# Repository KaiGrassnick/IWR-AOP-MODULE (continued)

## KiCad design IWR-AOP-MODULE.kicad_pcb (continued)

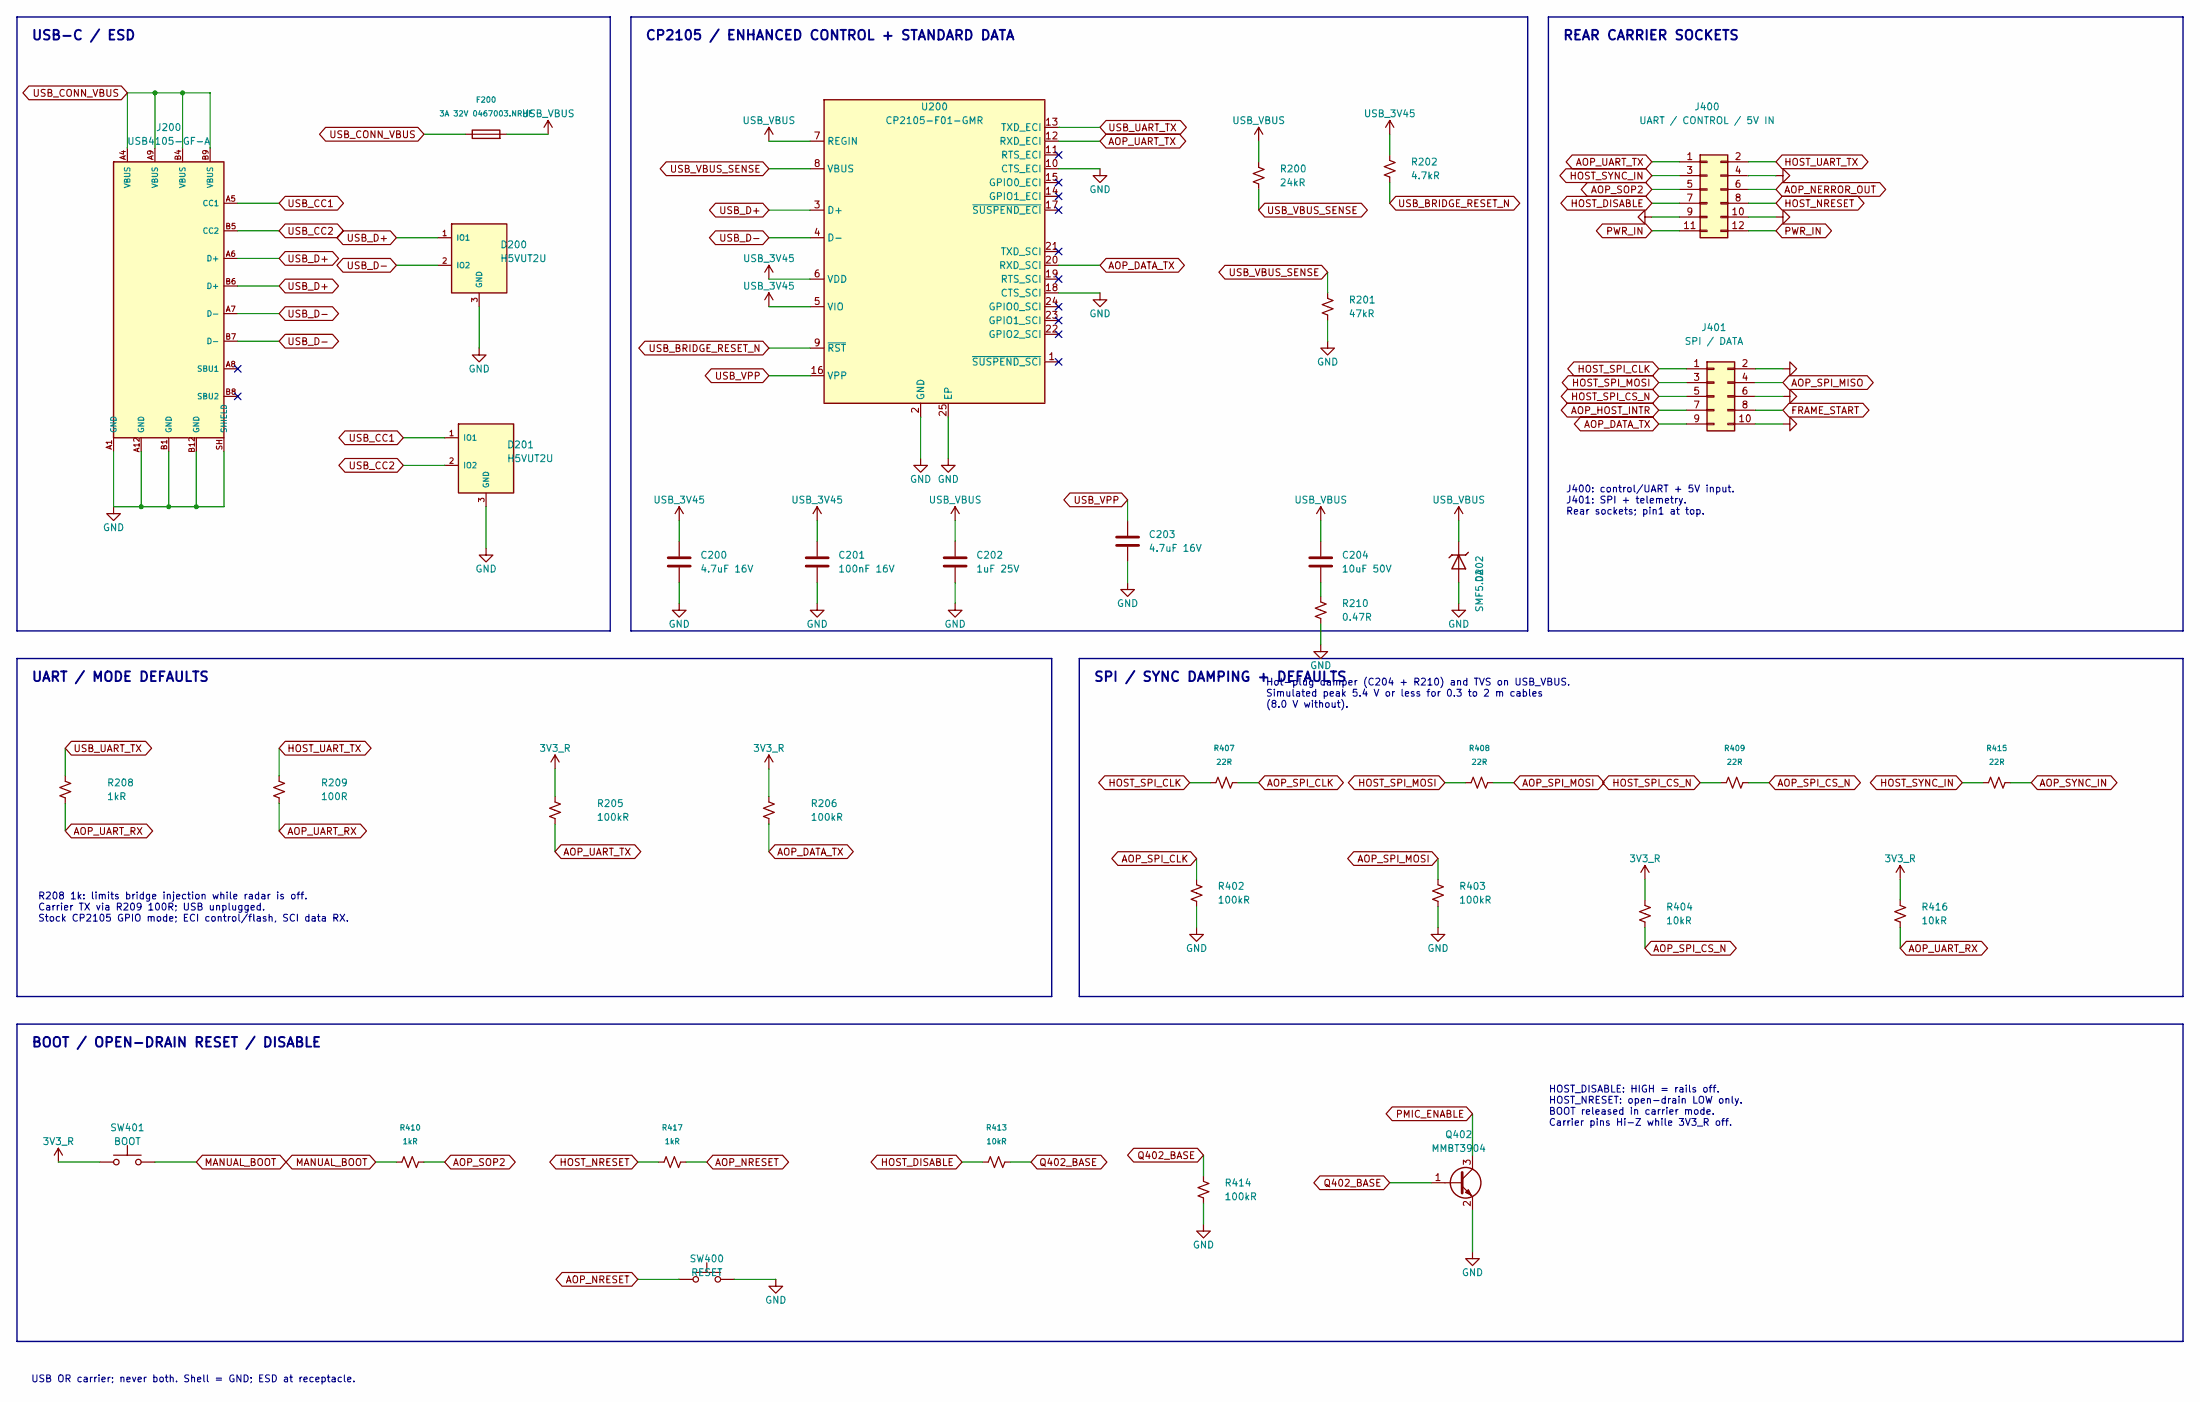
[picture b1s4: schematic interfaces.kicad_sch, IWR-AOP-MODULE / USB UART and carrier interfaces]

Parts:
C200, C203: 4.7uF 16V; C_0805_2012Metric; MPN CL21A475KAQNNNE; LCSC C1779
C201: 100nF 16V; C_0402_1005Metric; MPN CL05B104KO5NNNC; LCSC C1525
C202: 1uF 25V; C_0805_2012Metric; MPN CL21B105KBFNNNE; LCSC C28323
C204: 10uF 50V; C_1206_3216Metric; MPN CL31A106KBHNNNE; LCSC C13585
D200, D201: H5VUT2U; SOT-23; MPN H5VUT2U; LCSC C20615824
D202: SMF5.0A; D_SOD-123F; MPN SMF5.0A; LCSC C193402
F200: 3A 32V 0467003.NRHF; Fuse_0603_1608Metric; MPN 0467003.NRHF; LCSC C99558
J200: USB4105-GF-A; USB_C_Receptacle_GCT_USB4105-xx-A_16P_TopMnt_Horizontal; MPN USB4105-GF-A; LCSC C3020560
J400: UART / CONTROL / 5V IN; HCTL_PM254-2-06-S-8.5; MPN PM254-2-06-S-8.5; LCSC C3975151
J401: SPI / DATA; HCTL_PM254-2-05-S-8.5; MPN PM254-2-05-S-8.5; LCSC C3975150
Q402: MMBT3904; SOT-23; MPN MMBT3904; LCSC C20526
R200: 24kR; R_0402_1005Metric; MPN 0402WGF2402TCE; LCSC C25769
R201: 47kR; R_0402_1005Metric; MPN 0402WGF4702TCE; LCSC C25792
R202: 4.7kR; R_0402_1005Metric; MPN 0402WGF4701TCE; LCSC C25900
R205, R206, R402, R403, R414: 100kR; R_0402_1005Metric; MPN 0402WGF1003TCE; LCSC C25741
R208, R410, R417: 1kR; R_0402_1005Metric; MPN 0402WGF1001TCE; LCSC C11702
R209: 100R; R_0402_1005Metric; MPN 0402WGF1000TCE; LCSC C25076
R210: 0.47R; R_0603_1608Metric; MPN 0603WAF470LT5E; LCSC C23411
R404, R413, R416: 10kR; R_0402_1005Metric; MPN 0402WGF1002TCE; LCSC C25744
R407, R408, R409, R415: 22R; R_0402_1005Metric; MPN 0402WGF220JTCE; LCSC C25092
SW400: RESET; XKB_TS-1187A-B-A-B_5.1x5.1mm; MPN TS-1187A-B-A-B; LCSC C318884
SW401: BOOT; XKB_TS-1187A-B-A-B_5.1x5.1mm; MPN TS-1187A-B-A-B; LCSC C318884
U200: CP2105-F01-GMR; QFN-24-1EP_4x4mm_P0.5mm_EP2.7x2.6mm; MPN CP2105-F01-GMR; LCSC C109102

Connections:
3V3_R: R205.1, R206.1, R404.1, R416.1, SW401.1; also elsewhere on the board
AOP_DATA_TX: J401.9, R206.2, U200.20 (RXD_SCI); also elsewhere on the board
AOP_HOST_INTR: J401.7; also elsewhere on the board
AOP_NERROR_OUT: J400.6; also elsewhere on the board
AOP_NRESET: R417.2, SW400.1; also elsewhere on the board
AOP_SOP2: J400.5, R410.2; also elsewhere on the board
AOP_SPI_CLK: R402.1, R407.2; also elsewhere on the board
AOP_SPI_CS_N: R404.2, R409.2; also elsewhere on the board
AOP_SPI_MISO: J401.4; also elsewhere on the board
AOP_SPI_MOSI: R403.1, R408.2; also elsewhere on the board
AOP_SYNC_IN: R415.2; also elsewhere on the board
AOP_UART_RX: R208.2, R209.2, R416.2; also elsewhere on the board
AOP_UART_TX: J400.1, R205.2, U200.12 (RXD_ECI); also elsewhere on the board
FRAME_START: J401.8; also elsewhere on the board
GND: C200.2, C201.2, C202.2, C203.2, D200.3 (GND), D201.3 (GND), D202.2 (A), J200.A1 (GND), J200.A12 (GND), J200.B1 (GND), J200.B12 (GND), J200.SH (SHIELD), J400.4, J400.9, J400.10, J401.2, J401.6, J401.10, Q402.2 (E), R201.2, R210.2, R402.2, R403.2, R414.2, SW400.2, U200.2 (GND), U200.10 (CTS_ECI), U200.18 (CTS_SCI), U200.25 (EP); also elsewhere on the board
HOST_DISABLE: J400.7, R413.1
HOST_NRESET: J400.8, R417.1
HOST_SPI_CLK: J401.1, R407.1
HOST_SPI_CS_N: J401.5, R409.1
HOST_SPI_MOSI: J401.3, R408.1
HOST_SYNC_IN: J400.3, R415.1
HOST_UART_TX: J400.2, R209.1
MANUAL_BOOT: R410.1, SW401.2
unnamed: C204.2, R210.1
PMIC_ENABLE: Q402.3 (C); also elsewhere on the board
PWR_IN: J400.11, J400.12; also elsewhere on the board
Q402_BASE: Q402.1 (B), R413.2, R414.1
USB_3V45: C200.1, C201.1, R202.1, U200.5 (VIO), U200.6 (VDD)
USB_BRIDGE_RESET_N: R202.2, U200.9 (~RST)
USB_CC1: D201.1 (IO1), J200.A5 (CC1); also elsewhere on the board
USB_CC2: D201.2 (IO2), J200.B5 (CC2); also elsewhere on the board
USB_CONN_VBUS: F200.1, J200.A4 (VBUS), J200.A9 (VBUS), J200.B4 (VBUS), J200.B9 (VBUS)
USB_D+: D200.1 (IO1), J200.A6 (D+), J200.B6 (D+), U200.3 (D+)
USB_D-: D200.2 (IO2), J200.A7 (D-), J200.B7 (D-), U200.4 (D-)
USB_UART_TX: R208.1, U200.13 (TXD_ECI)
USB_VBUS: C202.1, C204.1, D202.1 (K), F200.2, R200.1, U200.7 (REGIN); also elsewhere on the board
USB_VBUS_SENSE: R200.2, R201.1, U200.8 (VBUS)
USB_VPP: C203.1, U200.16 (VPP)

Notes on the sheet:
USB-C / ESD
CP2105 / ENHANCED CONTROL + STANDARD DATA
REAR CARRIER SOCKETS
J400: control/UART + 5V input. J401: SPI + telemetry. Rear sockets; pin1 at top.
UART / MODE DEFAULTS
R208 1k: limits bridge injection while radar is off. Carrier TX via R209 100R; USB unplugged. Stock CP2105 GPIO mode; ECI control/flash, SCI data RX.
SPI / SYNC DAMPING + DEFAULTS
BOOT / OPEN-DRAIN RESET / DISABLE
HOST_DISABLE: HIGH = rails off. HOST_NRESET: open-drain LOW only. BOOT released in carrier mode. Carrier pins Hi-Z while 3V3_R off.
USB OR carrier; never both. Shell = GND; ESD at receptacle.
Hot-plug damper (C204 + R210) and TVS on USB_VBUS. Simulated peak 5.4 V or less for 0.3 to 2 m cables (8.0 V without).

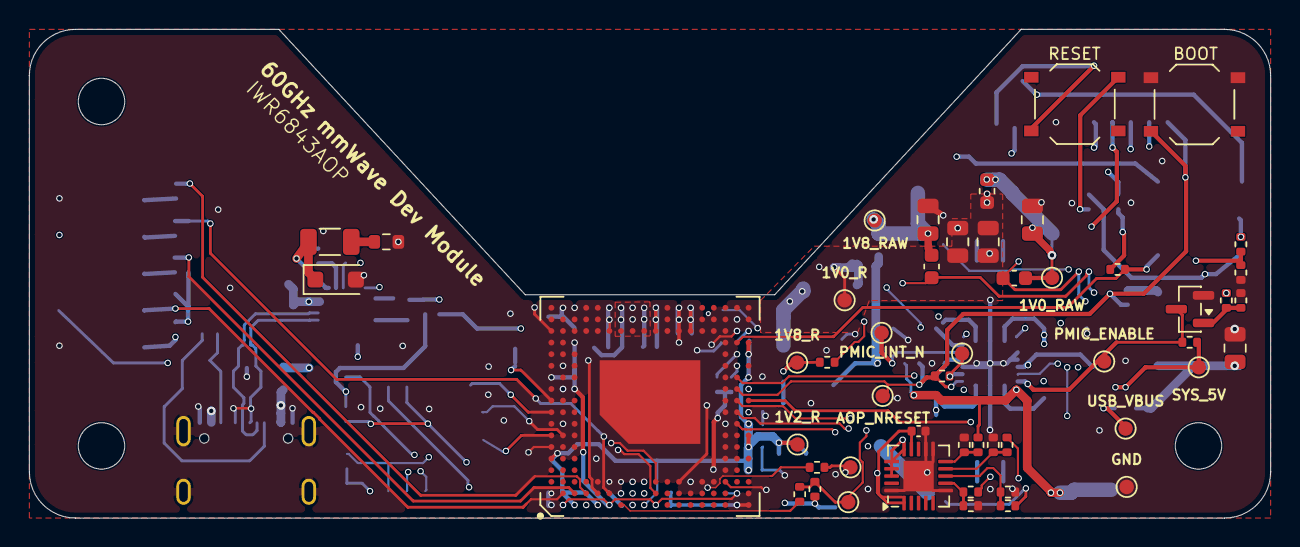
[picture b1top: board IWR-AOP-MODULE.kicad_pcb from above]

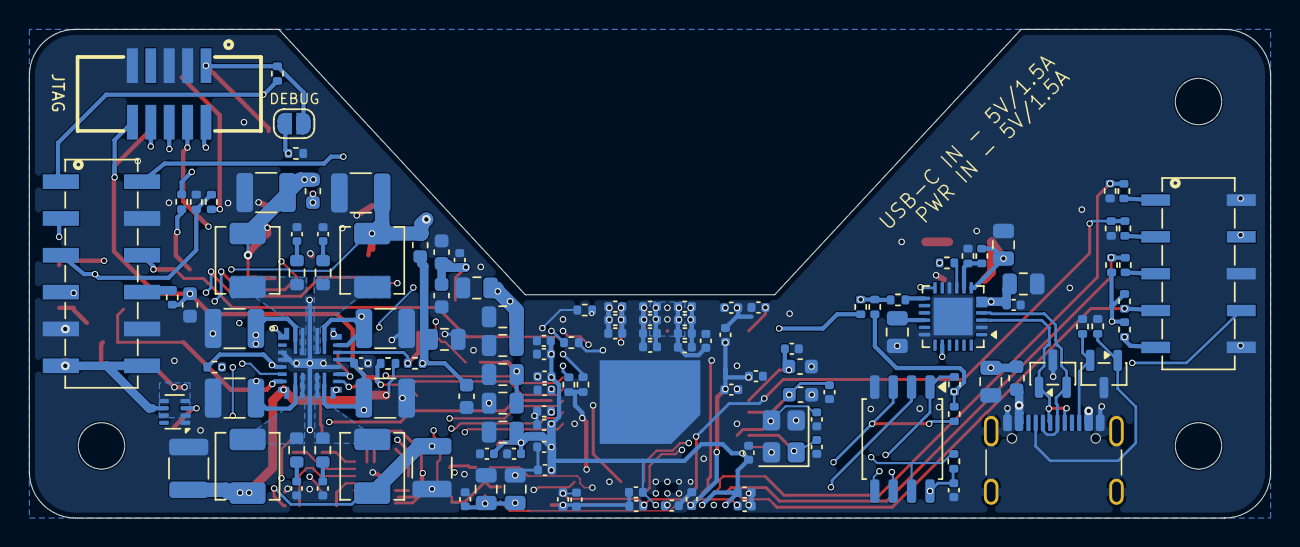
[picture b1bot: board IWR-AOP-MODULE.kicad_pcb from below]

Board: 6 copper layers, 85.6 x 33.7 mm, 186 parts (132 on the bottom side), 83 nets.

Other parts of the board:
H1, H3, H4: MountingHole_3.2mm_M3
HS300: Heat sink 14x14x6 (HSB03-141406 / ICK BGA 14x14x6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
TH300: AOP_ALP180_DieThermalPad

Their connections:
GND: TH300.1; also elsewhere on the board

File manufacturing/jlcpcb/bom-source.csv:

"Comment","Designator","Footprint","LCSC","Qty","MPN","Manufacturer","Tolerance","Rating"
"0R","R314,R605,R606","Resistor_SMD:R_0402_1005Metric","C17168","3","0402WGF0000TCE","UNI-ROYAL(Uniroyal Elec)","",""
"18pF","C346,C347","Capacitor_SMD:C_0402_1005Metric","C1549","2","0402CG180J500NT","FH (Guangdong Fenghua Advanced Tech)","",""
"390pF","C614,C615,C616,C617","Capacitor_SMD:C_0402_1005Metric","C76967","4","GRM1555C1H391JA01D","Murata Electronics","5%","C0G 50V"
"47nF","C345","Capacitor_SMD:C_0402_1005Metric","C77017","1","GRM155R71E473KA88D","Murata","",""
"100nF","C301,C302,C303,C304,C305,C306,C307,C308,C309,C310,C311,C314,C315,C316,C317,C318,C319,C322,C323,C324,C325,C326,C327,C328,C329,C330,C331,C332,C333,C335,C336,C338,C340,C342,C343,C344,C348,C604,C606,C622,C623,C706","Capacitor_SMD:C_0402_1005Metric","C1525","42","CL05B104KO5NNNC","Samsung Electro-Mechanics","",""
"0.47uH","L600,L601,L602,L603","Inductor_SMD:L_Sunlord_MWSA0402S","C6331050","4","MWSA0402S-R47MT","Sunlord","",""
"1uF","C313,C321,C337,C339","Capacitor_SMD:C_0603_1608Metric","C15849","4","CL10A105KB8NNNC","Samsung Electro-Mechanics","",""
"1uF","C631,C632","Capacitor_SMD:C_0603_1608Metric","C15849","2","CL10A105KB8NNNC","Samsung Electro-Mechanics","","X5R 50V"
"4.7uF","C341","Capacitor_SMD:C_0603_1608Metric","C19666","1","CL10A475KO8NNNC","Samsung Electro-Mechanics","",""
"10uF","C300,C312,C320,C334","Capacitor_SMD:C_0805_2012Metric","C15850","4","CL21A106KAYNNNE","Samsung Electro-Mechanics","",""
"10uF","C620,C621,C629","Capacitor_SMD:C_0805_2012Metric","C86038","3","GRM21BR71A106KE51L","Murata Electronics","10%","X7R 10V"
"22uF","C600,C601,C602,C603,C610,C611,C612,C613","Capacitor_SMD:C_1210_3225Metric","C21397","8","GRM32ER71E226KE15L","Murata Electronics","10%","X7R 25V"
"22uF","C624,C625,C626,C628,C630,C633","Capacitor_SMD:C_0805_2012Metric","C45783","6","CL21A226MAQNNNE","Samsung Electro-Mechanics","20%","X5R 25V"
"0.47R","R210","Resistor_SMD:R_0603_1608Metric","C23411","1","0603WAF470LT5E","UNI-ROYAL(Uniroyal Elec)","",""
"1kR","R208,R410,R417","Resistor_SMD:R_0402_1005Metric","C11702","3","0402WGF1001TCE","UNI-ROYAL(Uniroyal Elec)","",""
"3.9R","R610,R611,R612,R613","Resistor_SMD:R_0603_1608Metric","C482845","4","RC0603FR-073R9L","YAGEO","1%","100mW"
"4.7kR","R202","Resistor_SMD:R_0402_1005Metric","C25900","1","0402WGF4701TCE","UNI-ROYAL(Uniroyal Elec)","",""
"10kR","R133,R300,R304,R305,R306,R307,R308,R309,R310,R311,R312,R313,R404,R413,R416,R600,R601,R602,R603","Resistor_SMD:R_0402_1005Metric","C25744","19","0402WGF1002TCE","UNI-ROYAL(Uniroyal Elec)","",""
"12kR","R627","Resistor_SMD:R_0402_1005Metric","C25752","1","0402WGF1202TCE","UNI-ROYAL(Uniroyal Elec)","",""
"15kR","R621,R623,R625,R626","Resistor_SMD:R_0402_1005Metric","C25756","4","0402WGF1502TCE","UNI-ROYAL(Uniroyal Elec)","",""
"22R","R407,R408,R409,R415,R628,R629","Resistor_SMD:R_0402_1005Metric","C25092","6","0402WGF220JTCE","UNI-ROYAL(Uniroyal Elec)","",""
"24kR","R200","Resistor_SMD:R_0402_1005Metric","C25769","1","0402WGF2402TCE","UNI-ROYAL(Uniroyal Elec)","",""
"27kR","R624","Resistor_SMD:R_0402_1005Metric","C25771","1","0402WGF2702TCE","UNI-ROYAL(Uniroyal Elec)","",""
"47kR","R201,R622","Resistor_SMD:R_0402_1005Metric","C25792","2","0402WGF4702TCE","UNI-ROYAL(Uniroyal Elec)","",""
"100R","R209","Resistor_SMD:R_0402_1005Metric","C25076","1","0402WGF1000TCE","UNI-ROYAL(Uniroyal Elec)","",""
"100kR","R205,R206,R402,R403,R414,R620","Resistor_SMD:R_0402_1005Metric","C25741","6","0402WGF1003TCE","UNI-ROYAL(Uniroyal Elec)","",""
"40MHz","Y300","Crystal:Crystal_SMD_3225-4Pin_3.2x2.5mm","C18214314","1","XL2EL89COI-111YLC-40M","YXC Crystal Oscillators","",""
"100nF 16V","C201","Capacitor_SMD:C_0402_1005Metric","C1525","1","CL05B104KO5NNNC","Samsung Electro-Mechanics","",""
"10uF 10V","C140","Capacitor_SMD:C_0805_2012Metric","C86038","1","GRM21BR71A106KE51L","Murata Electronics","",""
"10uF 50V","C204","Capacitor_SMD:C_1206_3216Metric","C13585","1","CL31A106KBHNNNE","Samsung Electro-Mechanics","",""
"1uF 25V","C100,C202","Capacitor_SMD:C_0805_2012Metric","C28323","2","CL21B105KBFNNNE","Samsung Electro-Mechanics","",""
"26R@100MHz / 6A","FB600,FB601,FB602","Inductor_SMD:L_0603_1608Metric","C88981","3","BLM18KG260TN1D","Murata","",""
"3A 32V 0467003.NRHF","F200","Fuse:Fuse_0603_1608Metric","C99558","1","0467003.NRHF","Littelfuse","",""
"4.7uF 16V","C200,C203","Capacitor_SMD:C_0805_2012Metric","C1779","2","CL21A475KAQNNNE","Samsung Electro-Mechanics","",""
"5.1kR 1%","R100,R101","Resistor_SMD:R_0402_1005Metric","C25905","2","0402WGF5101TCE","UNI-ROYAL(Uniroyal Elec)","",""
"BOOT","SW401","IWR-AOP-MODULE:XKB_TS-1187A-B-A-B_5.1x5.1mm","C318884","1","TS-1187A-B-A-B","XKB Connection","",""
"CP2105-F01-GMR","U200","Package_DFN_QFN:QFN-24-1EP_4x4mm_P0.5mm_EP2.7x2.6mm","C109102","1","CP2105-F01-GMR","Silicon Laboratories","",""
"H5VUT2U","D200,D201","Package_TO_SOT_SMD:SOT-23","C20615824","2","H5VUT2U","hongjiacheng","",""
"IWR6843ARQGALPR","U300","IWR-AOP-MODULE:BGA180C80P18X18_1500X1500X97N","C2871887","1","IWR6843ARQGALPR","Texas Instruments","",""
"LM66200DRLR","U117","Package_TO_SOT_SMD:SOT-583-8","C3235556","1","LM66200DRLR","Texas Instruments","",""
"LP87524JRNFRQ1","U600","IWR-AOP-MODULE:Texas_RNF0026C_LP87524J","C701982","1","LP87524JRNFRQ1","Texas Instruments","",""
"MMBT3904","Q402","Package_TO_SOT_SMD:SOT-23","C20526","1","MMBT3904","Jiangsu Changjing Electronics Technology Co., Ltd.","",""
"MX25L3233FM2I-08G","U301","Package_SO:SOIC-8_5.3x5.3mm_P1.27mm","C190802","1","MX25L3233FM2I-08G","Macronix","",""
"RADAR JTAG","J301","IWR-AOP-MODULE:XKB_X1270WVS-2x05B-9TV01_2x05_P1.27mm_Vertical","C2962219","1","X1270WVS-2x05B-9TV01","XKB Connection","",""
"RESET","SW400","IWR-AOP-MODULE:XKB_TS-1187A-B-A-B_5.1x5.1mm","C318884","1","TS-1187A-B-A-B","XKB Connection","",""
"SMF5.0A","D202","Diode_SMD:D_SOD-123F","C193402","1","SMF5.0A","ElecSuper","",""
"SPI / DATA","J401","IWR-AOP-MODULE:HCTL_PM254-2-05-S-8.5","C3975150","1","PM254-2-05-S-8.5","HCTL","",""
"TPS386000RGPR","U601","Package_DFN_QFN:TQFN-20-1EP_4x4mm_P0.5mm_EP2.1x2.1mm","C702221","1","TPS386000RGPR","Texas Instruments","",""
"UART / CONTROL / 5V IN","J400","IWR-AOP-MODULE:HCTL_PM254-2-06-S-8.5","C3975151","1","PM254-2-06-S-8.5","HCTL","",""
"USB4105-GF-A","J200","Connector_USB:USB_C_Receptacle_GCT_USB4105-xx-A_16P_TopMnt_Horizontal","C3020560","1","USB4105-GF-A","Global Connector Technology","",""

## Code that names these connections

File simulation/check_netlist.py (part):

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      "14": "1V2_R", "15": "AOP_NRESET", "16": "PMIC_PGOOD", "17": "GND", "18": "SYS_5V",
      "19": "PMIC_INT_N", "20": "SYS_5V", "21": "/Radar PMIC/FB_B3", "22": "SYS_5V", "23": "PMIC_SW3",
      "24": "GND", "25": "PMIC_SW2", "26": "SYS_5V", "27": "GND"}
names = {"1": "FB_B2", "3": "CLKIN", "7": "EN1", "8": "FB_B0", "14": "FB_B1", "15": "EN2/GPIO2",
         "16": "PGOOD", "18": "VANA", "20": "NRST", "21": "FB_B3"}
for pad, want in lp.items():
    chk(f"U600 LP87524J pin {pad} {names.get(pad, '')}", pin("U600", pad) == want, f"{pin('U600', pad)} (want {want})")
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        ok and vmax < lo_reg, f"band starts at {lo_reg:.3f} V")
chk("R604 not fitted: PGOOD is not a reset source", "dnp" in P["R604"].get("attr", []))
# radar I2C master to the PMIC (SWRS237C pin-mux: G3 I2C_SCL mode 2, G1 I2C_SDA mode 2)
chk("U300 G3 (I2C_SCL) -> R605 -> PMIC_SCL", pin("U300", "G3") == "AOP_I2C_SCL" and set(P["R605"]["pads"].values()) == {"AOP_I2C_SCL", "PMIC_SCL"})
chk("U300 G1 (I2C_SDA) -> R606 -> PMIC_SDA", pin("U300", "G1") == "AOP_I2C_SDA" and set(P["R606"]["pads"].values()) == {"AOP_I2C_SDA", "PMIC_SDA"})
# USB hot-plug damper and TVS
chk("C204 + R210 series damper across USB_VBUS", P["C204"]["pads"]["1"] == "USB_VBUS" and P["C204"]["pads"]["2"] == P["R210"]["pads"]["1"]
    and P["R210"]["pads"]["2"] == "GND", f"{P['C204']['value']} + {P['R210']['value']}")
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
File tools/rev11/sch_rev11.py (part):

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        def fn(l):
            return l.replace(f'IWR-AOP-MODULE:PWR_{a}"', f'IWR-AOP-MODULE:PWR_{b}"').replace(f'"Value" "{a}"', f'"Value" "{b}"')
        return fn
    # FB_B2 / FB_B3: the power symbol on each feedback pin becomes a net label; the sense network
    # (R628/C631, R629/C632) is drawn in the supervisor block below.
    for pwr, fb in (("#PWR8028", "FB_B2"), ("#PWR8038", "FB_B3")):
        i = s.idx(pwr)
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    s.edit("#PWR8046", swap("1V8_R", "3V3_R"))
    # PGOOD is no longer a reset source by default
    s.edit("R604", lambda l: prop(l.replace("(dnp no)", "(dnp yes)"), "Description",
                                  "DNP option: fitted, PGOOD also asserts reset. Not fitted, reset is U601 + GPIO2."))
    # Ferrites: BLM18KG260TN1D (26 ohm, 6 A, 7 mohm max) in place of the 120 ohm part of the TI EVM. About a
    # quarter of the inductance: the filter still meets the 4 MHz ripple limit with margin, and the dip
    # a fast chirp current edge causes at the radar is roughly halved (simulation/run_loadstep.py).
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        s.L[i] = re.sub(r'\(text "[^"]*"', lambda m: f'(text "{new}"', s.L[i])
    retext("Kelvin sense after ferrite", "4 MHz; short VIN/PGND loops.\\nFB2/3: DC sense at the radar (R628/R629),\\nAC sense at the buck output (C631/C632).")
    retext("RC fallback", "R604 DNP: PGOOD is observed (TP613), not a reset source.\\nC605 DNP, footprint kept.\\nR600/601: I2C pull-ups to 3V3_R; bus master is the radar (R605/R606).")
    retext("open-drain reset sinks", "Reset sinks on AOP_NRESET (all open-drain):\\nU601 supervisor (all four rails), PMIC GPIO2 (falls with EN1),\\nSW400, J301.10, carrier through R417.")

    # extra bulk at the buck outputs: 2 x 22 uF local on each rail
    d = "Buck output bulk at the PMIC, inside the regulation loop (2 x 22 uF local)."
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    # SENSE4H unused -> GND
    s.wire(X - 15.24, Y, X - 34.29, Y); s.wire(X - 34.29, Y, X - 34.29, Y + 2.54); s.power("GND", X - 34.29, Y + 2.54)
    # MR -> VDD (no internal pull-up)
    s.wire(X - 15.24, Y + 5.08, X - 17.78, Y + 5.08); s.glabel("SYS_5V", X - 17.78, Y + 5.08, 180)
    # WDI -> GND, watchdog unused
    s.wire(X - 15.24, Y + 7.62, X - 17.78, Y + 7.62); s.wire(X - 17.78, Y + 7.62, X - 17.78, Y + 10.16); s.power("GND", X - 17.78, Y + 10.16)
    for dy in (-10.16, -7.62, -5.08, -2.54):
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    for dy in (-7.62, -5.08):
        s.junction(X + 20.32, Y + dy)
    s.junction(X + 20.32, Y - 10.16)
    s.wire(X + 20.32, Y - 10.16, X + 25.4, Y - 10.16); s.glabel("AOP_NRESET", X + 25.4, Y - 10.16, 0)
    for dy in (2.54, 5.08, 7.62, 10.16, 12.7, 15.24):
        s.nc(X + 15.24, Y + dy)
    s.wire(X, Y - 15.24, X, Y - 20.32); s.glabel("SYS_5V", X, Y - 20.32, 90)
    for dx in (-2.54, 0, 2.54):
        s.wire(X + dx, Y + 20.32, X + dx, Y + 22.86)
    s.wire(X - 2.54, Y + 22.86, X + 2.54, Y + 22.86); s.junction(X, Y + 22.86); s.power("GND", X, Y + 22.86)
    # U601 decoupling
    s.clone("C604", "C606", 290.83, 327.66, Description="U601 VDD decoupling")
    s.wire(290.83, 323.85, 290.83, 320.04); s.glabel("SYS_5V", 290.83, 320.04, 90)
    s.wire(290.83, 331.47, 290.83, 335.28); s.power("GND", 290.83, 335.28)

    # I2C: radar (G3 SCL, G1 SDA) -> PMIC, series 0R links as on the TI EVM
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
